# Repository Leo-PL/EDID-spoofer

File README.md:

# EDID Spoofer

A simple board, that helps tinkering with VESA DDC
- Override EDID on a display for custom resolutions
- Provide a EDID to the PC for sinks which lack EDID, like with BNC inputs
- Act as a dummy plug for servers for Intel AMT
- Sniff or interfere with DDC communication between the graphics card and the display

## Parts used:

- 1x DE-15HD THT plug (towards graphics card).
- 1x DE-15HD THT receptacle (towards display).
- [24LCS22A](https://www.microchip.com/en-us/product/24LCS22A), [24LC21A](https://www.microchip.com/en-us/product/24LC21A), or compatible VESA DDC1/DDC2 EEPROM. A generic 24C02 should work too.
- 1 3x 10k 0805 SMD resistors.
- 1x 100nF 0805 SMD capacitor.
- Generic 4-pin header for programming or external bus access.

## Programming

First programming can be done even if write protection is enabled, which is set by default using JP1 jumper.
Chip locks itself when address 0x7F (the EDID checksum) is written.
For programming, you can use SNANDer, i2c-tools or any other tool compatible with I²C EEPROMs.
If using ordinary 24C02, be sure to keep WP pin low, as this is A2 pin on that part, otherwise chip address won't match.
DDC1 and write protection also won't work in this case.

## Redistribution

Project contents are freely redistributable in any form. Please see the [license](LICENSE).

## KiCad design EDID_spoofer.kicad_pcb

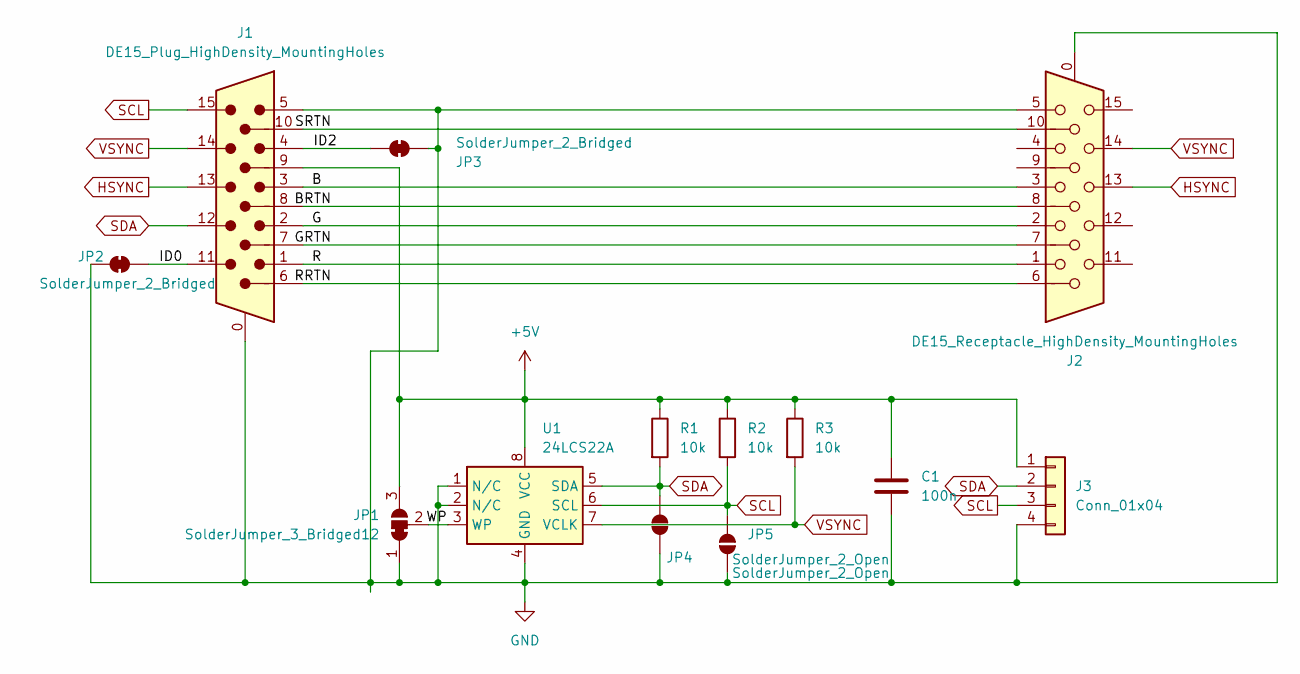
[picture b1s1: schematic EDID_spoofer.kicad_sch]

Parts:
C1: 100n; C_0805_2012Metric
J1: DE15_Plug_HighDensity_MountingHoles; DSUB-15-HD_Male_Horizontal_P2.29x1.98mm_EdgePinOffset8.35mm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
J2: DE15_Receptacle_HighDensity_MountingHoles; DSUB-15-HD_Female_Horizontal_P2.29x1.98mm_EdgePinOffset8.35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
J3: Conn_01x04; PinHeader_1x04_P2.54mm_Vertical
JP1: SolderJumper_3_Bridged12; SolderJumper-3_P1.3mm_Bridged12_RoundedPad1.0x1.5mm_NumberL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
JP2, JP3: SolderJumper_2_Bridged; SolderJumper-2_P1.3mm_Bridged_RoundedPad1.0x1.5mm
JP4, JP5: SolderJumper_2_Open; SolderJumper-2_P1.3mm_Open_RoundedPad1.0x1.5mm
R1, R2, R3: 10k; R_0805_2012Metric
U1: 24LCS22A; SO-8_3.9x4.9mm_P1.27mm

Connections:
+5V: C1.1, J1.9, J3.1, JP1.3 (B), R1.1, R2.1, R3.1, U1.8 (VCC)
/B: J1.3, J2.3
/BRTN: J1.8, J2.8
/G: J1.2, J2.2
/GRTN: J1.7, J2.7
/ID0: J1.11, JP2.2 (B)
/ID2: J1.4, JP3.2 (B)
/R: J1.1, J2.1
/RRTN: J1.6, J2.6
/SRTN: J1.10, J2.10
/WP: JP1.2 (C), U1.3 (WP)
GND: C1.2, J1.0, J1.5, J2.0, J2.5, J3.4, JP1.1 (A), JP2.1 (A), JP3.1 (A), JP4.1 (A), JP5.1 (A), U1.1 (N/C), U1.2 (N/C), U1.4 (GND)
HSYNC: J1.13, J2.13
SCL: J1.15, J3.3, JP5.2 (B), R2.2, U1.6 (SCL)
SDA: J1.12, J3.2, JP4.2 (B), R1.2, U1.5 (SDA)
VSYNC: J1.14, J2.14, R3.2, U1.7 (VCLK)

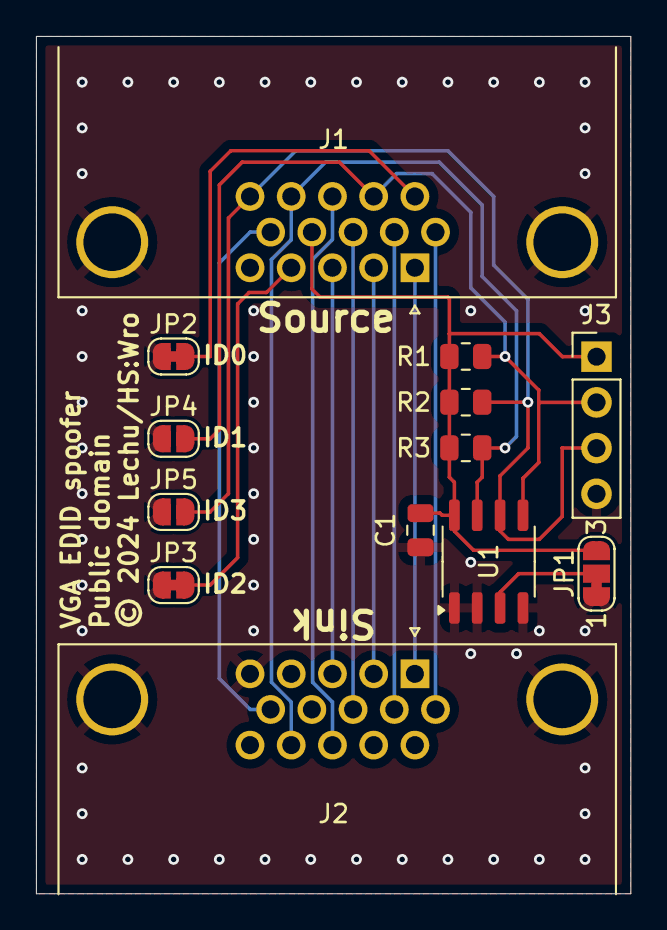
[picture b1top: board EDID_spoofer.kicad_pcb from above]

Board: 2 copper layers, 33.0 x 47.6 mm, 13 parts (0 on the bottom side), 16 nets.

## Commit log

2024-06-20 edid-spoofer: initial version
2024-06-21 Add DDC1 ID0-3 jumpers
    Allow configuration of DDC1 monitor ID bits 0-3.
    Defaults to ID0 and ID2 grounded, ID1 and ID3 open -
    - Color monitor which supports 1024x768.
    ID1 and ID3 are shared with SDA and SCL, hence unset by default.
    Also layout and signal integrity improvements.

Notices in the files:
EDID_spoofer.kicad_pcb:
Public domain
© 2024 Lechu/HS:Wro
